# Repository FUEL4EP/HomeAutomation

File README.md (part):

# HomeAutomation   

## Home Automation Repository von FUEL4EP

### Homebrew [Asksinpp](https://asksinpp.de/) Sensoren und benötigtes [CCU3/openCCU Addon](https://github.com/FUEL4EP/HomeAutomation/releases/latest):

#### Sensoren:

|  | Name | Beschreibung | 🔋Batterie-/<br/>⚡️Netzbetrieb |
|--------|--------|--------|:--------:|
| | [HB-UNI-SENSOR1-CO2-SCD30](https://github.com/FUEL4EP/HomeAutomation/tree/master/AsksinPP_developments/sketches/HB-UNI-Sensor1-CO2_SCD30) | genauer NDIR CO2 Sensor<br/>_basierend auf Sensirion SCD30<br/>Akku- oder Netzbetrieb<br/>und WebUI Offseteinstellung_ | 🔋 ⚡ |
| | [HB-UNI-SENSOR1-AQ-BME680](https://github.com/FUEL4EP/HomeAutomation/tree/master/AsksinPP_developments/sketches/HB-UNI-Sensor1-AQ-BME680) | selbstkalibrierender Air Quality Sensor<br/>_basierend auf Bosch BME680<br/>und multipler linearer Regression<br/>und WebUI Offseteinstellung_ (aLF Version)| 🔋 |
| | [HB-UNI-SENSOR1-AQ-BME680_KF](https://github.com/FUEL4EP/HomeAutomation/tree/master/AsksinPP_developments/sketches/HB-UNI-Sensor1-AQ-BME680_KF) | selbst kalibrierender Air Quality Sensor<br/>basierend auf Bosch BME680<br/>und Kalman Filter<br/>und WebUI Offseteinstellung (aLF Version)| 🔋 |
| | [HB-UNI-SENSOR1-AQ-BME680_KF_DEBUG](https://github.com/FUEL4EP/HomeAutomation/tree/master/AsksinPP_developments/sketches/HB-UNI-Sensor1-AQ-BME680_KF_DEBUG) | selbst kalibrierender Air Quality Sensor<br/>basierend auf Bosch BME680<br/>und Kalman Filter<br/>und WebUI Offseteinstellung (aLF Version)<br/>nur für Debugzwecke!| 🔋 |
| | [HB-UNI-SENSOR1-TH-SHT75](https://github.com/FUEL4EP/HomeAutomation/tree/master/AsksinPP_developments/sketches/HB-UNI-Sensor1-TH-SHT75)  | hoch genauer TH Sensor<br/>_basierend auf Sensirion SHT75<br/>NEU: und 24h Tagesmittelwerttemperatur<br/>und WebUI Offseteinstellung_ | 🔋 |
| | [HB-UNI-SENSOR1-THPD-BME280](https://github.com/FUEL4EP/HomeAutomation/tree/master/AsksinPP_developments/sketches/HB-UNI-Sensor1-THPD-BME280) | THPD Sensor<br/>_basierend auf Bosch BME280<br/>mit Taupunkttemperatur<br/>und absoluter Luftfeuchte<br/>und WebUI Offseteinstellung_ | 🔋 |
| | [HB-UNI-SENSOR1-THPD-SHT85](https://github.com/FUEL4EP/HomeAutomation/tree/master/AsksinPP_developments/sketches/HB-UNI-Sensor1-THPD-SHT85)  | hoch genauer THPD Sensor<br/>_basierend auf Sensirion SHT85 und Bosch BME280<br/>mit Taupunkttemperatur<br/>und absoluter Luftfeuchte<br/>NEU: und 24h- und 7 Tagesmittelwerttemperaturen<br/>und WebUI Offseteinstellung_ | 🔋 |
| | [HB-UNI-SENSOR1-RAD-AL53](https://github.com/FUEL4EP/HomeAutomation/tree/master/AsksinPP_developments/sketches/HB-UNI-Sensor1-RAD-AL53) | Radioaktivitätssensor für Alpha-, Beta- und Gammastrahlung<br/>_basierend auf Teviso AL53 Sensor<br/>mit gleitender Mittelwertbildung über 7 Tage_ | 🔋 |
| | [HB-UNI-SENSOR1-AQ-BME680_KF_rLF](https://github.com/FUEL4EP/HomeAutomation/tree/master/AsksinPP_developments/sketches/HB-UNI-Sensor1-AQ-BME680_KF_rLF) <br/>- NEU -| selbstkalibrierender Air Quality Sensor<br/>basierend auf Bosch BME680<br/>und Kalman Filter<br/>und WebUI Offseteinstellung (rLF Version) | 🔋 |
| | [HB-UNI-SENSOR1-AQ-BME680_KF_rLF_DEBUG](https://github.com/FUEL4EP/HomeAutomation/tree/master/AsksinPP_developments/sketches/HB-UNI-Sensor1-AQ-BME680_KF_rLF_DEBUG) <br/>- NEU -| selbst kalibrierender Air Quality Sensor<br/>basierend auf Bosch BME680<br/>und Kalman Filter<br/>und WebUI Offseteinstellung (rLF Version)<br/>nur für Debugzwecke!| 🔋 |
| | [HB-UNI-SenAct-4-4-SC_DS](https://github.com/FUEL4EP/HomeAutomation/tree/master/AsksinPP_developments/sketches/HB-UNI-SenAct-4-4-SC_DS)<br/> - NEU -| 3x Schaltaktor für Betrieb an einem **Netzfreischalter** - Akkubetrieb im Standby, automatische Ladeschaltung - bei Aktivierung eines Aktors wird die Netzspannung zugeschaltet und am Ende wieder abgeschaltet - geringer Standby-Verbrauch von ca. 1 mA @ 5V| 🔋 ⚡ |
| | [HB-UNI-SENSOR1-THD-SHT45](https://github.com/FUEL4EP/HomeAutomation/tree/master/AsksinPP_developments/sketches/HB-UNI-Sensor1-THD-SHT45)<br/> - NEU -| hoch genauer THD Sensor<br/>basierend auf Sensirion SHT45 <br/>mit Taupunkttemperatur,<br/>absoluter Luftfeuchte<br/>und gleitendem Mittelwert der Temperatur über 24 Stunden und 7 Tage<br/>| 🔋 |
| | [HB-UNI-Sensor1-THPD-SHT45_BME280](https://github.com/FUEL4EP/HomeAutomation/tree/master/AsksinPP_developments/sketches/HB-UNI-Sensor1-THPD-SHT45_BME280)<br/> - NEU -| hoch genauer THPD Sensor<br/>basierend auf Sensirion SHT45 und Bosch BME280 <br/>mit Taupunkttemperatur,<br/>absoluter Luftfeuchte<br/>und gleitendem Mittelwert der Temperatur über 24 Stunden und 7 Tage<br/>| 🔋 |
| | [Range_test_beacon](https://github.com/FUEL4EP/HomeAutomation/tree/master/AsksinPP_developments/sketches/Range_test_beacon)<br/> - NEU -| 868,3Mhz Funkbake um die Reichweite eines HF-Übertragungskanals zu ermitteln (nur für Testzwecke)<br/>| 🔋 |
| | [FreqTest_range_test_with_distant_beacon](https://github.com/FUEL4EP/HomeAutomation/tree/master/AsksinPP_developments/sketches/FreqTest_range_test_with_distant_beacon)<br/> - NEU -| spezielle Version von FreqTest um die Reichweite eines HF-Übertragungskanals zu ermitteln (nur für Testzwecke)<br/>| 🔋 |
| | [HB-UNI-Sensor1-THP_MA-AHT20_BMP280](https://github.com/FUEL4EP/HomeAutomation/tree/master/AsksinPP_developments/sketches/HB-UNI-Sensor1-THP_MA-AHT20_BMP280)<br/> - NEU -|  genauer THP Außensensor zur Beobachtung des Klimawandels<br/>basierend auf Aosong AHT20 und Bosch BME280 <br/>mit gleitenden Temperaturmittelwerten für 1 Jahr, 1 Monat, 1 Woche und 1 Tag<br>mit nichtflüchtigem FRAM-Speicher| 🔋 |

<br/>
<br/>
<br/>

#### CCU3/openCCU Addon:

[hb-ep-devices-addon](https://github.com/FUEL4EP/HomeAutomation/releases/latest)

- bitte die .tgz Datei als Zusatzsoftware auf der CCU3/openCCU installieren

<br/>

#### Arduino Bibliotheken:

| Name | Beschreibung | Datenblatt |
|--------|--------|:--------:|
| [ABLIC_S35770](https://github.com/FUEL4EP/HomeAutomation/tree/master/AsksinPP_developments/libraries/ABLIC_S35770) | Arduino Bibliothek für ABLIC S-35770<br/>24-Bit Binärzähler mit I2C Schnittstelle | [datasheet](https://www.ablic.com/en/doc/datasheet/counter_ic/S35770_I_E.pdf)|
| [avr_stl](https://github.com/FUEL4EP/HomeAutomation/tree/master/AsksinPP_developments/libraries/avr_stl) | Arduino C++ Standard Library (ArduinoSTL)<br/>abgeleitet von [Giampaolo Mancini](https://github.com/manchoz/avr_stl.git) | [README.md](https://github.com/FUEL4EP/HomeAutomation/tree/master/AsksinPP_developments/libraries/avr_st/README.md)|
| [FRAM Bibliothek](https://github.com/FUEL4EP/HomeAutomation/tree/master/AsksinPP_developments/sketches/HB-UNI-Sensor1-THP_MA-AHT20_BMP280/Sensors/Fujitsu_MB85RS2MTPF_FRAM_circular_buffer.h) | Arduino C++ Bibliothek für Fujitsu 2x 2MBit MB85RS2MTPF SPI FRAM | Source Code |

<br/>

#### PCBs:

| Name | Beschreibung | 3D Ansicht |
|--------|--------|:--------:|
| [HB-UNI-SEN-BATT_FUEL4EP](https://github.com/FUEL4EP/HomeAutomation/tree/master/AsksinPP_developments/PCBs/HB-UNI-SEN-BATT_FUEL4EP) | AsksinPP Platine basierend auf [Tindie Pro Mini XL - v2 - ATmega 1284p](https://www.tindie.com/products/prominimicros/pro-mini-xl-v2-atmega-1284p/) oder Arduino Pro Mini| [3D Ansicht](https://github.com/FUEL4EP/HomeAutomation/tree/master/AsksinPP_developments/PCBs/HB-UNI-SEN-BATT_FUEL4EP/PNGs/HB-UNI-SEN-BATT_FUEL4EP_PCB_top_3D.png)|
| [HB-UNI-SEN-BATT_E07-868MS10_FUEL4EP](https://github.com/FUEL4EP/HomeAutomation/tree/master/AsksinPP_developments/PCBs/HB-UNI-SEN-BATT_E07-868MS10_FUEL4EP) | AsksinPP Platine basierend auf<br/> [Tindie Pro Mini XL - v2 - ATmega 1284p](https://www.tindie.com/products/prominimicros/pro-mini-xl-v2-atmega-1284p/) oder Arduino Pro Mini<br/> und [eByte E07-868MS10 Sendemodul](https://www.rcscomponents.kiev.ua/datasheets/e07-868ms10_usermanual_en_v1_20.pdf)| [3D Ansicht](https://github.com/FUEL4EP/HomeAutomation/tree/master/AsksinPP_developments/PCBs/HB-UNI-SEN-BATT_E07-868MS10_FUEL4EP/PNGs/HB-UNI-SEN-BATT_E07-868MS10_FUEL4EP_PCB_3D_top.png)|
| [HB-UNI-SEN-BATT_ATMega1284P_E07-900MM10S_FUEL4EP](https://github.com/FUEL4EP/HomeAutomation/tree/master/AsksinPP_developments/PCBs/HB-UNI-SEN-BATT_ATMega1284P_E07-900MM10S_FUEL4EP) | AsksinPP Platine mit SMD Bestückung:<br/> ATMega1284P <br/>[eByte E07-900MM10S Sendemodul](https://www.cdebyte.com/products/E07-900MM10S)<br/>optionalem Aufwärtwandler TPS61221<br/>[optionalem e-Paper Waveshare 1,54 Zoll](https://www.waveshare.com/wiki/1.54inch_e-Paper_Module)| [3D Ansicht 1](https://github.com/FUEL4EP/HomeAutomation/tree/master/AsksinPP_developments/PCBs/HB-UNI-SEN-BATT_ATMega1284P_E07-900MM10S_FUEL4EP/PNGs/HB-UNI-SEN-BATT_ATMega1284P_E07-900MM10S_FUEL4EP_PCB_top_3D.png)<br/>[3D Ansicht 2](https://github.com/FUEL4EP/HomeAutomation/tree/master/AsksinPP_developments/PCBs/HB-UNI-SEN-BATT_ATMega1284P_E07-900MM10S_FUEL4EP/PNGs/HB-UNI-SEN-BATT_ATMega1284P_E07-900MM10S_FUEL4EP_PCB_top_3D_with_epaper_option.png)|
| [HB-UNI-SEN-BATT_ATMega1284P_E07-868MS10_FUEL4EP](https://github.com/FUEL4EP/HomeAutomation/tree/master/AsksinPP_developments/PCBs/HB-UNI-SEN-BATT_ATMega1284P_E07-868MS10_FUEL4EP) | AsksinPP Platine mit SMD Bestückung:<br/> ATMega1284P <br/>[eByte E07-868MS10 Sendemodul](https://www.rcscomponents.kiev.ua/datasheets/e07-868ms10_usermanual_en_v1_20.pdf)<br/>optionalem Aufwärtwandler TPS61221<br/>[optionalem e-Paper Waveshare 1,54 Zoll](https://www.waveshare.com/wiki/1.54inch_e-Paper_Module)| [3D Ansicht 1](https://github.com/FUEL4EP/HomeAutomation/tree/master/AsksinPP_developments/PCBs/HB-UNI-SEN-BATT_ATMega1284P_E07-868MS10_FUEL4EP/PNGs/HB-UNI-SEN-BATT_ATMega1284P_E07-868MS10_FUEL4EP_PCB_top_3D.png)<br/>[3D Ansicht 2](https://github.com/FUEL4EP/HomeAutomation/tree/master/AsksinPP_developments/PCBs/HB-UNI-SEN-BATT_ATMega1284P_E07-868MS10_FUEL4EP/PNGs/HB-UNI-SEN-BATT_ATMega1284P_E07-868MS10_FUEL4EP_PCB_top_3D_with_epaper_option.png)|
| [HB-UNI-SEN-BATT_ATMega1284P_E07-868MS10_FRAM_FUEL4EP](https://github.com/FUEL4EP/HomeAutomation/tree/master/AsksinPP_developments/PCBs/HB-UNI-SEN-BATT_ATMega1284P_E07-868MS10_FRAM_FUEL4EP) | AsksinPP Platine mit SMD Bestückung:<br/> ATMega1284P <br/>[eByte E07-868MS10 Sendemodul](https://www.rcscomponents.kiev.ua/datasheets/e07-868ms10_usermanual_en_v1_20.pdf)<br/>optionalem Aufwärtwandler TPS61221<br/>[optionalem e-Paper Waveshare 1,54 Zoll](https://www.waveshare.com/wiki/1.54inch_e-Paper_Module)<br/>optionalen 2x 2Mbit FRAM MB85RS2MTPF| [3D Ansicht 1](https://github.com/FUEL4EP/HomeAutomation/tree/master/AsksinPP_developments/PCBs/HB-UNI-SEN-BATT_ATMega1284P_E07-868MS10_FRAM_FUEL4EP/PNGs/HB-UNI-SEN-BATT_ATMega1284P_E07-868MS10_FRAM_FUEL4EP_PCB_top_3D.png)<br/>[3D Ansicht 2](https://github.com/FUEL4EP/HomeAutomation/tree/master/AsksinPP_developments/PCBs/HB-UNI-SEN-BATT_ATMega1284P_E07-868MS10_FRAM_FUEL4EP/PNGs/HB-UNI-SEN-BATT_ATMega1284P_E07-868MS10_FRAM_FUEL4EP_PCB_with_epaper_option.png)|
| [HB-UNI-SenAct-4-4-SC_DS_FUEL4EP](https://github.com/FUEL4EP/HomeAutomation/tree/master/AsksinPP_developments/PCBs/HB-UNI-SenAct-4-4-SC_DS_FUEL4EP) | AsksinPP Platine für Durchsteckmontage für 3xSchaltaktor für Betrieb an Netzfreischalter| [3D Ansicht](https://github.com/FUEL4EP/HomeAutomation/tree/master/AsksinPP_developments/PCBs/HB-UNI-SenAct-4-4-SC_DS_FUEL4EP/PNGs/HB-UNI-SenAct-4-4-SC_DS_FUEL4EP_PCB_top_3D.png)|
| [HB-UNI-SEN-BATT_E07-900M10S_FUEL4EP](https://github.com/FUEL4EP/HomeAutomation/tree/master/AsksinPP_developments/PCBs/HB-UNI-SEN-BATT_E07-900M10S_FUEL4EP) - NEU -| AsksinPP Platine basierend auf<br/> [Tindie Pro Mini XL - v2 - ATmega 1284p](https://www.tindie.com/products/prominimicros/pro-mini-xl-v2-atmega-1284p/) oder Arduino Pro Mini<br/> und [eByte E07-900M10S Sendemodul](https://www.manualslib.com/manual/2937348/Ebyte-E07-900m10s.html)| [3D Ansicht](https://github.com/FUEL4EP/HomeAutomation/tree/master/AsksinPP_developments/PCBs/HB-UNI-SEN-BATT_E07-900M10S_FUEL4EP/PNGs/HB-UNI-SEN-BATT_E07-900M10S_FUEL4EP_PCB_3D_top.png)|
| [HB-UNI-SEN-BATT_E07-900MM10S_FUEL4EP](https://github.com/FUEL4EP/HomeAutomation/tree/master/AsksinPP_developments/PCBs/HB-UNI-SEN-BATT_E07-900MM10S_FUEL4EP) - NEU -| AsksinPP Platine basierend auf<br/> [Tindie Pro Mini XL - v2 - ATmega 1284p](https://www.tindie.com/products/prominimicros/pro-mini-xl-v2-atmega-1284p/) oder Arduino Pro Mini<br/> und [eByte E07-900MM10S Sendemodul](https://www.cdebyte.com/pdf-down.aspx?id=1932)| [3D Ansicht](https://github.com/FUEL4EP/HomeAutomation/tree/master/AsksinPP_developments/PCBs/HB-UNI-SEN-BATT_E07-900MM10S_FUEL4EP/PNGs/HB-UNI-SEN-BATT_E07-900MM10S_FUEL4EP_PCB_3D_top.png)|
| [CC1101_868MHz_RF_Modul_FUEL4EP](https://github.com/FUEL4EP/HomeAutomation/tree/master/AsksinPP_developments/PCBs/CC1101_868MHz_RF_Modul_FUEL4EP) - NEU -| AsksinPP RF 868.3 MHz Funkmodule als Ersatz für eByte E07-868M10S| [3D Ansicht](https://github.com/FUEL4EP/HomeAutomation/tree/master/AsksinPP_developments/PCBs/CC1101_868MHz_RF_Modul_FUEL4EP/PNGs/CC1101_868MHz_RF_Modul_FUEL4EP_PCB_3D_top.png)|
| [CC1101_868MHz_UFL_RF_Modul_FUEL4EP](https://github.com/FUEL4EP/HomeAutomation/tree/master/AsksinPP_developments/PCBs/CC1101_868MHz_UFL_RF_Modul_FUEL4EP) - NEU -| AsksinPP RF 868.3 MHz Funkmodule als Ersatz für eByte E07-868M10S mit U.FL Antennenbuchse| [3D Ansicht](https://github.com/FUEL4EP/HomeAutomation/tree/master/AsksinPP_developments/PCBs/CC1101_868MHz_UFL_RF_Modul_FUEL4EP/PNGs/CC1101_868MHz_UFL_RF_Modul_FUEL4EP_PCB_3D_top.png)|
| [4Bit_I2C_Port_Expander_Module_FUEL4EP](https://github.com/FUEL4EP/HomeAutomation/tree/master/AsksinPP_developments/PCBs/4Bit_I2C_Port_Expander_Module_FUEL4EP) - NEU -| I2C Portexpander| [3D Ansicht](https://github.com/FUEL4EP/HomeAutomation/tree/master/AsksinPP_developments/PCBs/4Bit_I2C_Port_Expander_Module_FUEL4EP/PNGs/4Bit_I2C_Port_Expander_Module_FUEL4EP_PCB_3D_top.png)|
| [I2C_Module_BME280_FUEL4EP](https://github.com/FUEL4EP/HomeAutomation/tree/master/AsksinPP_developments/PCBs/I2C_Module_BME280_FUEL4EP) - NEU -| I2C BME280 THPD Sensor Modul| [3D Ansicht](https://github.com/FUEL4EP/HomeAutomation/tree/master/AsksinPP_developments/PCBs/I2C_Module_BME280_FUEL4EP/PNGs/I2C_Module_BME280_FUEL4EP_PCB_3D_top.png)|
| [I2C_Module_BME680_FUEL4EP](https://github.com/FUEL4EP/HomeAutomation/tree/master/AsksinPP_developments/PCBs/I2C_Module_BME680_FUEL4EP) - NEU -| I2C BME680 VOC Sensor Modul| [3D Ansicht](https://github.com/FUEL4EP/HomeAutomation/tree/master/AsksinPP_developments/PCBs/I2C_Module_BME680_FUEL4EP/PNGs/I2C_Module_BME680_FUEL4EP_PCB_3D_top.png)|
| [I2C_Module_SHT85_BME280_FUEL4EP](https://github.com/FUEL4EP/HomeAutomation/tree/master/AsksinPP_developments/PCBs/I2C_Module_SHT85_BME280_FUEL4EP) - NEU -| I2C SHT85 und BME280 THPD Sensor Modul| [3D Ansicht](https://github.com/FUEL4EP/HomeAutomation/tree/master/AsksinPP_developments/PCBs/I2C_Module_SHT85_BME280_FUEL4EP/PNGs/I2C_Module_SHT85_BME280_FUEL4EP_PCB_3D_top.png)|
| [I2C_Module_SHT45_BME280_FUEL4EP](https://github.com/FUEL4EP/HomeAutomation/tree/master/AsksinPP_developments/PCBs/I2C_Module_SHT45_BME280_FUEL4EP) - NEU -| I2C SHT45 und BME280 THPD Sensor Modul| [3D Ansicht](https://github.com/FUEL4EP/HomeAutomation/tree/master/AsksinPP_developments/PCBs/I2C_Module_SHT45_BME280_FUEL4EP/PNGs/I2C_Module_SHT45_BME280_FUEL4EP_PCB_3D_top.png)|
| [I2C_Module_SHT45_BME280_small_FUEL4EP](https://github.com/FUEL4EP/HomeAutomation/tree/master/AsksinPP_developments/PCBs/I2C_Module_SHT45_BME280_small_FUEL4EP) - NEU -| kleines I2C SHT45 und BME280 THPD Sensor Modul| [3D Ansicht](https://github.com/FUEL4EP/HomeAutomation/tree/master/AsksinPP_developments/PCBs/I2C_Module_SHT45_BME280_small_FUEL4EP/PNGs/I2C_Module_SHT45_BME280_small_FUEL4EP_PCB_3D_top.png)|
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
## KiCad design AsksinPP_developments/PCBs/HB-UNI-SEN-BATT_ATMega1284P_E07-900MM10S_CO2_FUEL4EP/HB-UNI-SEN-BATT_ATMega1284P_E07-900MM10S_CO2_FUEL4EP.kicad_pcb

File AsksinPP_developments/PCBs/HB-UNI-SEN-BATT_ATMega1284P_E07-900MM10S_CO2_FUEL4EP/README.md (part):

# HB-UNI-SEN-BATT_ATMega1284P_E07-900MM10S_CO2_FUEL4EP    

# DO NOT USE: THE PCB HAS FATAL ERRORS AND MUST BE REWORKED: KiCAD symbol and footprint of the FDN304P were wrong. Furthermore, for the I2C pass gates the FDN304P's capacitances are by far too big. The control circuit shown in GSS' data sheet CozIR-Blink-DataSheet-Rev-4.25_3.pdf on page 8 is WRONG and does not work! A rework is ongoing. 
  
# BITTE NICHT BENUTZEN: Die Platine hat fatale Fehler und muss neu erstellt werden: KiCAD Symbol und Footprint des FDN304P MOSFET Transistors sind falsch. Außerdem sind die Kapazitäten eines FDN304P Transistors als I2C Passgate viel zu hoch. Die Kontrollschaltung, die in dem GSS Datenblatt CozIR-Blink-DataSheet-Rev-4.25_3.pdf auf Seite 8  gezeigt wird ist falsch und funktioniert so nicht! Eine Überarbeitung ist im Gange.

**Platine für DIY AsksinPP NDIR-CO2-Sensor COZIR-BLINK-5000 mit extrem niedrigem Stromverbrauch :**
- speziell angepasst für [COZIR-LP3-5000 CozIR®-LP3 Low Power CO2 Sensor](https://www.co2meter.com/de-de/collections/1-percent-co2-sensor/products/cozir-lp3-co2-sensor?variant=32074932781174)
	- der CO2 Sensor ist käuflich erwerbbar z.B. bei Reichelt [COZIR-BLINK-NON-PIN-5000](https://www.reichelt.de/de/de/shop/produkt/ultra-low_power_co2_sensor_mit_power-cycling-308788?PROVID=2788&gad_source=1&gad_campaignid=1622074784)
	- ein Datenblatt des CO2 Sensors ist [hier](https://cdn.shopify.com/s/files/1/0019/5952/files/CozIR-LP3_Data_Sheet_Rev_4.6.pdf?v=1695834654)
	- Messbereich bis 5000 ppm CO2
- eingebauter SMD TQFP-44 [ATMega1284P](https://ww1.microchip.com/downloads/en/DeviceDoc/doc8059.pdf) mit 128kByte Programmspeicher, 16kByte SRAM, 4kByte EEPROM
-  als Funkmodul wird das [eByte E07-900MM10S Sendemodul](https://ebyteiot.com/products/ebyte-e07-900MM10Sti-cc1101-wireless-rf-module-868mhz-915mhz-ipex-stamp?_pos=2&_sid=bbf1d47dc&_ss=r) verwendet.
- U.FL Antennenbuchse als Bestückungsoption für eine externe Antenne
- kleines 10mmx10mm [eByte E07-900MM10S Sendemodul](https://ebyteiot.com/products/ebyte-e07-900MM10Sti-cc1101-wireless-rf-module-868mhz-915mhz-ipex-stamp?_pos=2&_sid=bbf1d47dc&_ss=r)
- Steckerleiste für [Waveshare ePaper Modul (1.54inch (B)](https://www.waveshare.com/product/1.54inch-e-paper-module.htm)
- Bestückungsoption für [Waveshare ePaper Modul (1.54inch (B)](https://www.waveshare.com/product/1.54inch-e-paper-module.htm)
- Bestückungsoption für [TPS61221 Aufwärtswandler](https://www.ti.com/lit/ds/symlink/tps61221.pdf?ts=1634546965861&ref_url=https%253A%252F%252Fwww.ti.com%252Fproduct%252FTPS61221) bei NiMH Akkumulatorbetrieb
- die Bestückungsoptionen ePaper wurden noch nicht validiert!
- 3 LEDS für die Anzeige der CO2-Konzentration mit kurz aufblinkenden LEDs (rot, gelb, grün)
- Bestückungsoption für Piezosignalgeber [POPESQ® Signalgeber Piezo Buzzer 13x13x2.5mm](https://www.amazon.de/dp/B0C57D9RQ8) zur akustischen Warnung bei zu hoher CO2-Konzentration
- eingebauter [BOSCH BME280 I2C Sensor](https://www.bosch-sensortec.com/products/environmental-sensors/humidity-sensors-bme280/) zur Luftdruckkompensation des CO2-Sensors
- alle SMD Bausteine sind mit dem JLCPCB SMT Bestückungsservice kostengünstig und qualitativ hochwertig bestückbar

## Status

- die Platine wurde bei JLCPCB bestellt und ist nun in der Fertigung ist aber noch nicht validiert. Nutzung auf eigenes Risiko!

## Credits

- diese Platine ist von Alexander Reinerts Platine [HB-UNI-SEN-BATT](https://github.com/alexreinert/PCB/tree/master/HB-UNI-SEN-BATT) abgeleitet.
- vielen Dank an Alexander Reinert für die Vorarbeit
- der Abstand der Batteriehalter wurde vergrößert, damit der COZIR-LP3-5000 CozIR®-LP3 Low Power CO2 Sensor dazwischen passt.

## Eigenschaften

- abgeleitet aus [HB-UNI-SEN-BATT](https://github.com/alexreinert/PCB/tree/master/HB-UNI-SEN-BATT)
- kompletter Datensatz für KiCAD 8 auf Github verfügbar:
    + 'git clone https://github.com/FUEL4EP/HomeAutomation.git' oder als [ZIP-Datei](https://github.com/FUEL4EP/HomeAutomation/archive/refs/heads/master.zip)
    + die Platinendaten sind dann unter 'HomeAutomation/AsksinPP_developments/PCBs/HB-UNI-SEN-BATT_ATMega1284P_E07-900MM10S_CO2_FUEL4EP' direkt mit KiCAD aufrufbar
- neue Eigenschaften:
    + SMD Bestückung, wo möglich
    + SMD TQFP-44 [ATMega1284P](https://ww1.microchip.com/downloads/en/DeviceDoc/doc8059.pdf) mit 128kByte Programmspeicher, 16kByte SRAM, 4kByte EEPROM
    + Bestückungsoption für [Waveshare ePaper Modul (1.54inch (B)](https://www.waveshare.com/product/1.54inch-e-paper-module.htm)
    + Bestückungsoption für [TPS61221 Aufwärtswandler](https://www.ti.com/lit/ds/symlink/tps61221.pdf?ts=1634546965861&ref_url=https%253A%252F%252Fwww.ti.com%252Fproduct%252FTPS61221) bei NiMH Akkumulatorbetrieb
    + alle SMD Bausteine sind mit dem JLCPCB SMT Bestückungsservice kostengünstig und qualitativ hochwertig bestückbar, das ist also auch für Grobmotoriker wie mich geeignet :-)
    + Stiftleiste J10 mit Versorgungsspannungen zum Gehäuseoberteil oder Akkulademodul
    + als Funkmodul wird das [eByte E07-900MM10S Sendemodul](https://ebyteiot.com/products/ebyte-e07-900MM10Sti-cc1101-wireless-rf-module-868mhz-915mhz-ipex-stamp?_pos=2&_sid=bbf1d47dc&_ss=r) verwendet. Dieses ist qualitativ viel besser als die üblichen grünen noname 868 MHz Funkmodule.
    + das schafft Platz für eine 8-polige Stiftleiste J11 zum optionalen Anschluss eines [Waveshare ePaper Moduls (1.54inch (B)](https://www.waveshare.com/product/1.54inch-e-paper-module.htm). Der ATMega1284P hat auch genügend RAM für die Programmierung eines 200 Pixel x 200 Pixel e-Papermoduls.
    + JLCPCB BOM and CPL Dateien für SMT Service werden [bereitgestellt](./jlcpcb/production_files)

### Benötigte Bauteile:

- bedingt durch die SMT Service von JLCPCB sind nur noch wenige Durchsteckbauteile von Hand zu verlöten:
* e-Paper [Waveshare ePaper Moduls (1.54inch (B)](https://www.waveshare.com/product/1.54inch-e-paper-module.htm) (optional, Anschluss an J11)
* CO2 Sensor [COZIR-LP3-5000 CozIR®-LP3 Low Power CO2 Sensor](https://www.co2meter.com/de-de/collections/1-percent-co2-sensor/products/cozir-lp3-co2-sensor?variant=32074932781174)
* Piezosignalgeber [Amazon POPESQ® Signalgeber Piezo Buzzer 13x13x2.5mm](https://www.amazon.de/dp/B0C57D9RQ8) oder [Alibaba 13*13 MM SMD-Summer-Wandler Extern angetriebener Piezo 5 V 5 mA 4,1 kHz 75 dB Oberflächen montierte Lötpads FUET-1325 Piezo-Summer](https://www.alibaba.com/product-detail/13-13-MM-SMD-Buzzer-Transducer_62560653672.html)
* 2x Keystone 2460 Batteriehalter 1xAA, z.B. [SOS Electronic](https://www.soselectronic.com/de-de/products/keystone-electronics/keys2460-2460-135729)
* Stiftleiste RM 2mm 1x8 Pin (für ePaper)
* Stiftleisten RM 2,54mm (nach Bedarf)
* IRLU024N (optional für Verpolungsschutz)
* Versorgung durch NiMH Akkumulatoren und Aufwärtswandler ist vorbereitet (JP2)
* Bestückungsoption Aufwärtswandler siehe [Schaltplan](Schematics/HB-UNI-SEN-BATT_ATMega1284P_E07-900MM10S_CO2_FUEL4EP.pdf), unter KiCAD sind alle Referenzen eingetragen

### Aufbauhinweise

- es wird dringend angeraten, vor dem Einbau der I2C Sensoren durchzuführen
    + einen Frequenztest. Hier der Frequenztest für einen ATmega 1284p : [FreqTest_1284P.ino](../Supplements/FreqTest_1284P/FreqTest_1284P.ino)
    + einen Leckagetest. Hier der Leckagetest für einen ATmega 1284p : [SleepTest_1284P.ino](../Supplements/SleepTest_1284P/SleepTest_1284P.ino)
        + der Leckagestrom im Sleepmode sollte < 10 uA betragen

### Passende AsksinPP Projekte von FUEL4EP
   + [tbd](https://github.com/FUEL4EP/HomeAutomation/tree/master/AsksinPP_developments/sketches/tbd)
   + muss noch entwickelt werden

### Anschluss eines FTDI Debuggers

- zum Anschluss eines FTDI Debuggers an die 6-polige Stiftleiste J12 bitte ein [6 Pin Dupontkabel 2.54mm Buchse-Buchse 20 cm](https://www.roboter-bausatz.de/p/6-pin-dupontkabel-2.54mm-buchse-buchse-20-cm) verwenden

### Passendes Gehäuse
* tbd, muss noch entwickelt werden

### Hinweise
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
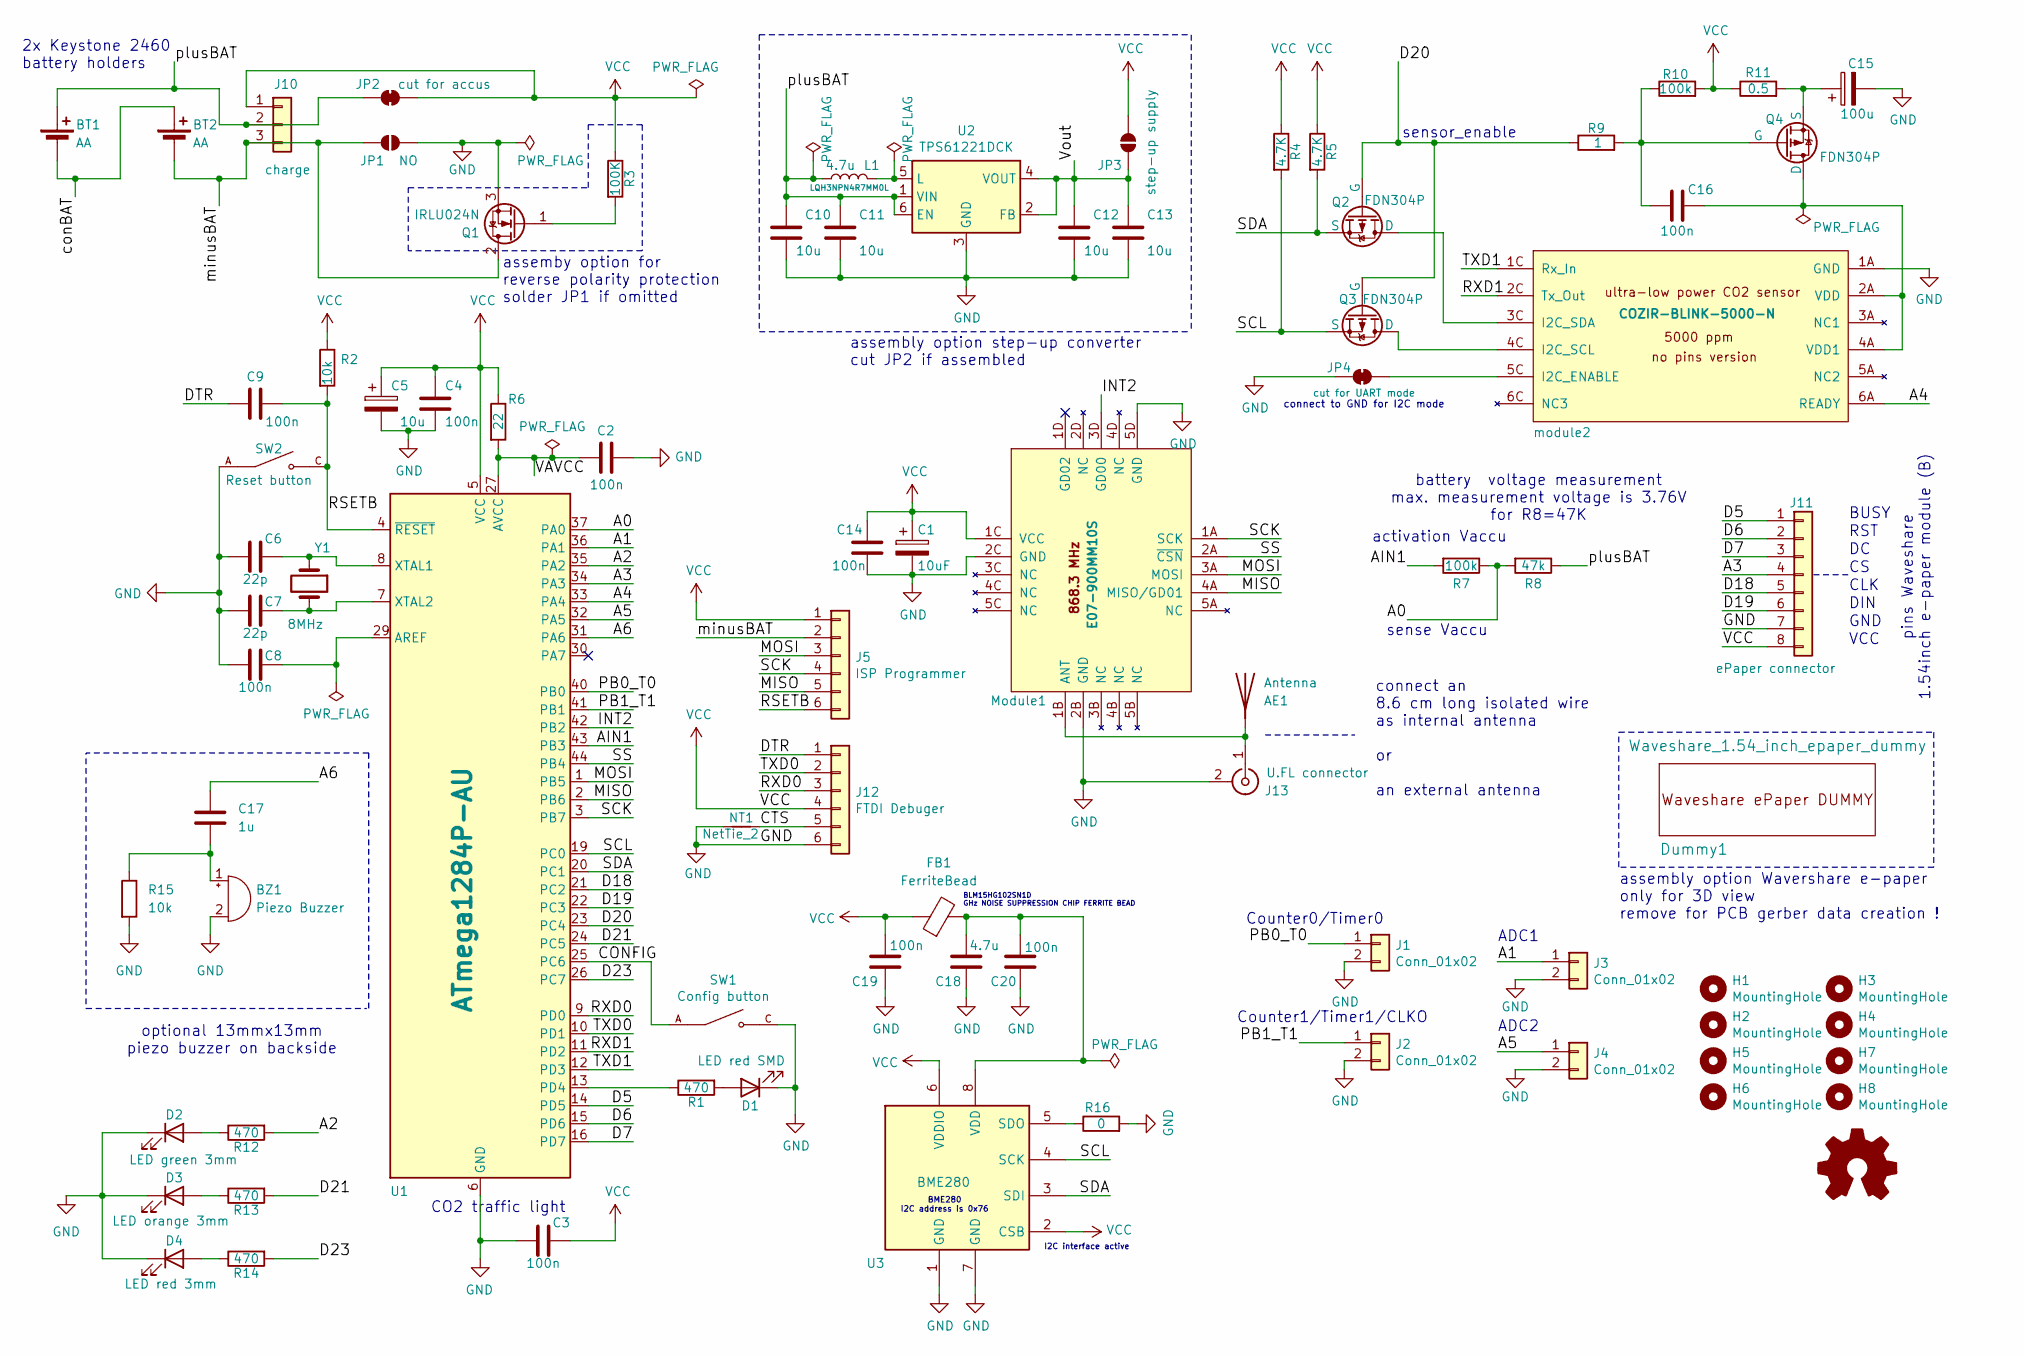
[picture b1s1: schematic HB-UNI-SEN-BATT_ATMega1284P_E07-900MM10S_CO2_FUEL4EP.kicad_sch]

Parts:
AE1: Antenna; SolderWire-0.1sqmm_1x01_D0.4mm_OD1mm
BT1, BT2: AA; BatteryHolder_Keystone_2460_1xAA
BZ1: Piezo Buzzer; Buzzer_SMD_POPESQ_POPESQ_13mm_13mm_2.5mm
C1: 10uF; C_0402_1005Metric; LCSC C15525
C2, C3, C4, C8, C9: 100n; C_0805_2012Metric; LCSC C28233
C5: 10u; C_1206_3216Metric_Pad1.33x1.80mm_HandSolder; LCSC C7171
C6, C7: 22p; C_0805_2012Metric; LCSC C1804
C10, C11, C12, C13: 10u; C_0805_2012Metric; LCSC C15850
C14: 100n; C_0402_1005Metric; LCSC C1525
C15: 100u; CP_EIA-6032-15_Kemet-U_Pad2.25x2.35mm_HandSolder; LCSC C16133
C16, C19, C20: 100n; C_0603_1608Metric; LCSC C14663
C17: 1u; C_0805_2012Metric_Pad1.18x1.45mm_HandSolder; LCSC C28323
C18: 4.7u; C_0603_1608Metric; LCSC C19666
D1: LED red SMD; LED_0805_2012Metric_Pad1.15x1.40mm_HandSolder; LCSC C84256
D2: LED green 3mm; LED_D3.0mm_angle_green
D3: LED orange 3mm; LED_D3.0mm_angle_orange
D4: LED red 3mm; LED_D3.0mm_angle_red
Dummy1: Waveshare_1.54_inch_epaper_dummy; Waveshare_ePaper_module
FB1: FerriteBead; L_0402_1005Metric; LCSC C76889
H1, H2, H3, H4: MountingHole; MountingHole_2.2mm_M2_Pad_Via
H5, H6, H7, H8: MountingHole; ePaper_MountingHole_M5
J1, J2, J3, J4: Conn_01x02; PinHeader_1x02_P2.54mm_Vertical
J5: ISP Programmer; PinHeader_1x06_P2.54mm_Vertical
J10: charge; PinHeader_1x03_P2.54mm_Vertical
J11: ePaper connector; PinSocket_1x08_P2.00mm_Vertical
J12: FTDI Debuger; PinHeader_1x06_P2.54mm_Vertical
J13: U.FL connector; U.FL_Molex_MCRF_73412-0110_Vertical
JP1: NO; SolderJumper-2_P1.3mm_Open_Pad1.0x1.5mm
JP2: cut for accus; SolderJumper-2_P1.3mm_Bridged_Pad1.0x1.5mm
JP3: step-up supply; SolderJumper-2_P1.3mm_Open_Pad1.0x1.5mm
JP4: cut for UART mode; SolderJumper-2_P1.3mm_Bridged_Pad1.0x1.5mm
L1: 4.7u; FUEL4EP_Inductor_SMD_1; LCSC C86077
LOGO1: Logo_Open_Hardware_Small; CC-BY-ND-SA
Module1: E07-900MM10S; eByte_E07-900MM10S; LCSC C5844212
NT1: NetTie_2; NetTie-2_SMD_Pad0.5mm
Q1: IRLU024N; TO-251-3_Vertical; LCSC C558184
Q2, Q3, Q4: FDN304P; SOT-23; LCSC C241803
R1, R12, R13, R14: 470; R_0805_2012Metric_Pad1.20x1.40mm_HandSolder; LCSC C17710
R2, R15: 10k; R_0805_2012Metric_Pad1.20x1.40mm_HandSolder; LCSC C17414
R3: 100K; R_0603_1608Metric_Pad0.98x0.95mm_HandSolder; LCSC C25803
R4, R5: 4.7K; R_0805_2012Metric_Pad1.20x1.40mm_HandSolder; LCSC C17673
R6: 22; R_0805_2012Metric_Pad1.20x1.40mm_HandSolder; LCSC C23345
R7: 100k; R_0805_2012Metric_Pad1.20x1.40mm_HandSolder; LCSC C149504
R8: 47k; R_0805_2012Metric_Pad1.20x1.40mm_HandSolder; LCSC C17713
R9: 1; R_0603_1608Metric; LCSC C22936
R10: 100k; R_0603_1608Metric; LCSC C25803
R11: 0.5; R_0603_1608Metric; LCSC C45312
R16: 0; R_0402_1005Metric; LCSC C17168
SW1: Config button; SW_TS-1187A-B-A-B; PARTREV A0; LCSC C318884
SW2: Reset button; SW_TS-1187A-B-A-B; PARTREV A0; LCSC C318884
U1: ATmega1284P-AU; TQFP-44_10x10mm_P0.8mm; LCSC C33575
U2: TPS61221DCK; Texas_R-PDSO-G6; LCSC C37055
U3: BME280; Bosch_LGA-8_2.5x2.5mm_P0.65mm_ClockwisePinNumbering; LCSC C92489
Y1: 8MHz; Crystal_SMD_5032-2Pin_5.0x3.2mm_HandSoldering; LCSC C115962
module2: COZIR-BLINK-5000-N

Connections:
/A0: R7.1, R8.2, U1.37 (PA0)
/A1: J3.1, U1.36 (PA1)
/A2: R12.2, U1.35 (PA2)
/A3: J11.4, U1.34 (PA3)
/A4: U1.33 (PA4), module2.6A (READY)
/A5: J4.1, U1.32 (PA5)
/A6: C17.1, U1.31 (PA6)
/AIN1: R7.2, U1.43 (PB3)
/CONFIG: SW1.A, SW1.B (e), U1.25 (PC6)
/CTS: J12.5, NT1.2
/D5: J11.1, U1.14 (PD5)
/D6: J11.2, U1.15 (PD6)
/D7: J11.3, U1.16 (PD7)
/D18: J11.5, U1.21 (PC2)
/D19: J11.6, U1.22 (PC3)
/D20: Q2.2 (G), Q3.2 (G), R9.1, U1.23 (PC4)
/D21: R13.2, U1.24 (PC5)
/D23: R14.2, U1.26 (PC7)
/DTR: C9.2, J12.1
/INT2: Module1.3D (GD00), U1.42 (PB2)
/MISO: J5.5, Module1.4A (MISO/GD01), U1.2 (PB6)
/MOSI: J5.3, Module1.3A (MOSI), U1.1 (PB5)
/PB0_T0: J1.1, U1.40 (PB0)
/PB1_T1: J2.1, U1.41 (PB1)
/RSETB: C9.1, J5.6, R2.2, SW2.C, SW2.D, U1.4 (~RESET)
/RXD0: J12.3, U1.9 (PD0)
/RXD1: U1.11 (PD2), module2.2C (Tx_Out)
/SCK: J5.4, Module1.1A (SCK), U1.3 (PB7)
/SCL: Q3.3 (S), R4.2, U1.19 (PC0), U3.4 (SCK)
/SDA: Q2.3 (S), R5.2, U1.20 (PC1), U3.3 (SDI)
/SS: Module1.2A (~CSN), U1.44 (PB4)
/TXD0: J12.2, U1.10 (PD1)
/TXD1: U1.12 (PD3), module2.1C (Rx_In)
/VAVCC: C2.2, R6.2, U1.27 (AVCC)
/Vout: C12.1, C13.1, JP3.1 (A), U2.2 (FB), U2.4 (VOUT)
/conBAT: BT1.2 (-), BT2.1 (+)
/minusBAT: BT2.2 (-), J5.2, J10.3, JP1.1 (A), Q1.2 (D)
/plusBAT: BT1.1 (+), C10.1, C11.1, J10.2, JP2.1 (A), L1.1, R8.1, U2.1 (VIN), U2.6 (EN)
GND: BZ1.2 (-), C1.2, C2.1, C3.2, C4.2, C5.2, C6.2, C7.2, C8.2, C10.2, C11.2, C12.2, C13.2, C14.2, C15.2, C18.2, C19.2, C20.2, D1.1 (K), D2.1 (K), D3.1 (K), D4.1 (K), J1.2, J2.2, J3.2, J4.2, J11.7, J12.6, J13.2 (Ext), JP1.2 (B), JP4.1 (A), Module1.2B (GND), Module1.2C (GND), Module1.5D (GND), NT1.1, Q1.3 (S), R15.2, R16.2, SW1.C, SW1.D, SW2.A, SW2.B (e), U1.6 (GND), U1.18 (GND), U1.28 (GND), U1.39 (GND), U2.3 (GND), U3.1 (GND), U3.7 (GND), module2.1A (GND)
unnamed: AE1.1 (A), J13.1 (In), Module1.1B (ANT)
unnamed: BZ1.1 (+), C17.2, R15.1
unnamed: D1.2 (A), R1.2
unnamed: D2.2 (A), R12.1
unnamed: D3.2 (A), R13.1
unnamed: D4.2 (A), R14.1
unnamed: JP4.2 (B), module2.5C (I2C_ENABLE)
unnamed: Q1.1 (G), R3.2
unnamed: Q2.1 (D), module2.3C (I2C_SDA)
unnamed: Q3.1 (D), module2.4C (I2C_SCL)
unnamed: C16.2, Q4.1 (D), module2.2A (VDD), module2.4A (VDD1)
unnamed: C16.1, Q4.2 (G), R9.2, R10.1
unnamed: C15.1, Q4.3 (S), R11.2
unnamed: C8.1, U1.29 (AREF)
unnamed: R1.1, U1.13 (PD4)
unnamed: C6.1, U1.8 (XTAL1), Y1.1
unnamed: C7.1, U1.7 (XTAL2), Y1.2
unnamed: L1.2, U2.5 (L)
unnamed: R16.1, U3.5 (SDO)
unnamed: C18.1, C20.1, FB1.2, U3.8 (VDD)
VCC: C1.1, C3.1, C4.1, C5.1, C14.1, C19.1, FB1.1, J5.1, J10.1, J11.8, J12.4, JP2.2 (B), JP3.2 (B), Module1.1C (VCC), R2.1, R3.1, R4.1, R5.1, R6.1, R10.2, R11.1, U1.5 (VCC), U1.17 (VCC), U1.38 (VCC), U3.2 (CSB), U3.6 (VDDIO)

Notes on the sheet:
connect to GND for I2C mode
RST
CLK
ADC2
connect an 8.6 cm long isolated wire as internal antenna or an external antenna
VCC
BME280 I2C address is 0x76
activation Vaccu
Counter1/Timer1/CLKO
assemby option for reverse polarity protection solder JP1 if omitted
BLM15HG102SN1D GHz NOISE SUPPRESSION CHIP FERRITE BEAD
Counter0/Timer0
ADC1
assembly option step-up converter cut JP2 if assembled
battery voltage measurement max. measurement voltage is 3.76V for R8=47K
pins Waveshare 1.54inch e-paper module (B)
sensor_enable
sense Vaccu
optional 13mmx13mm piezo buzzer on backside
2x Keystone 2460 battery holders
CO2 traffic light
GND
DIN
BUSY
I2C interface active
assembly option Wavershare e-paper only for 3D view remove for PCB gerber data creation !

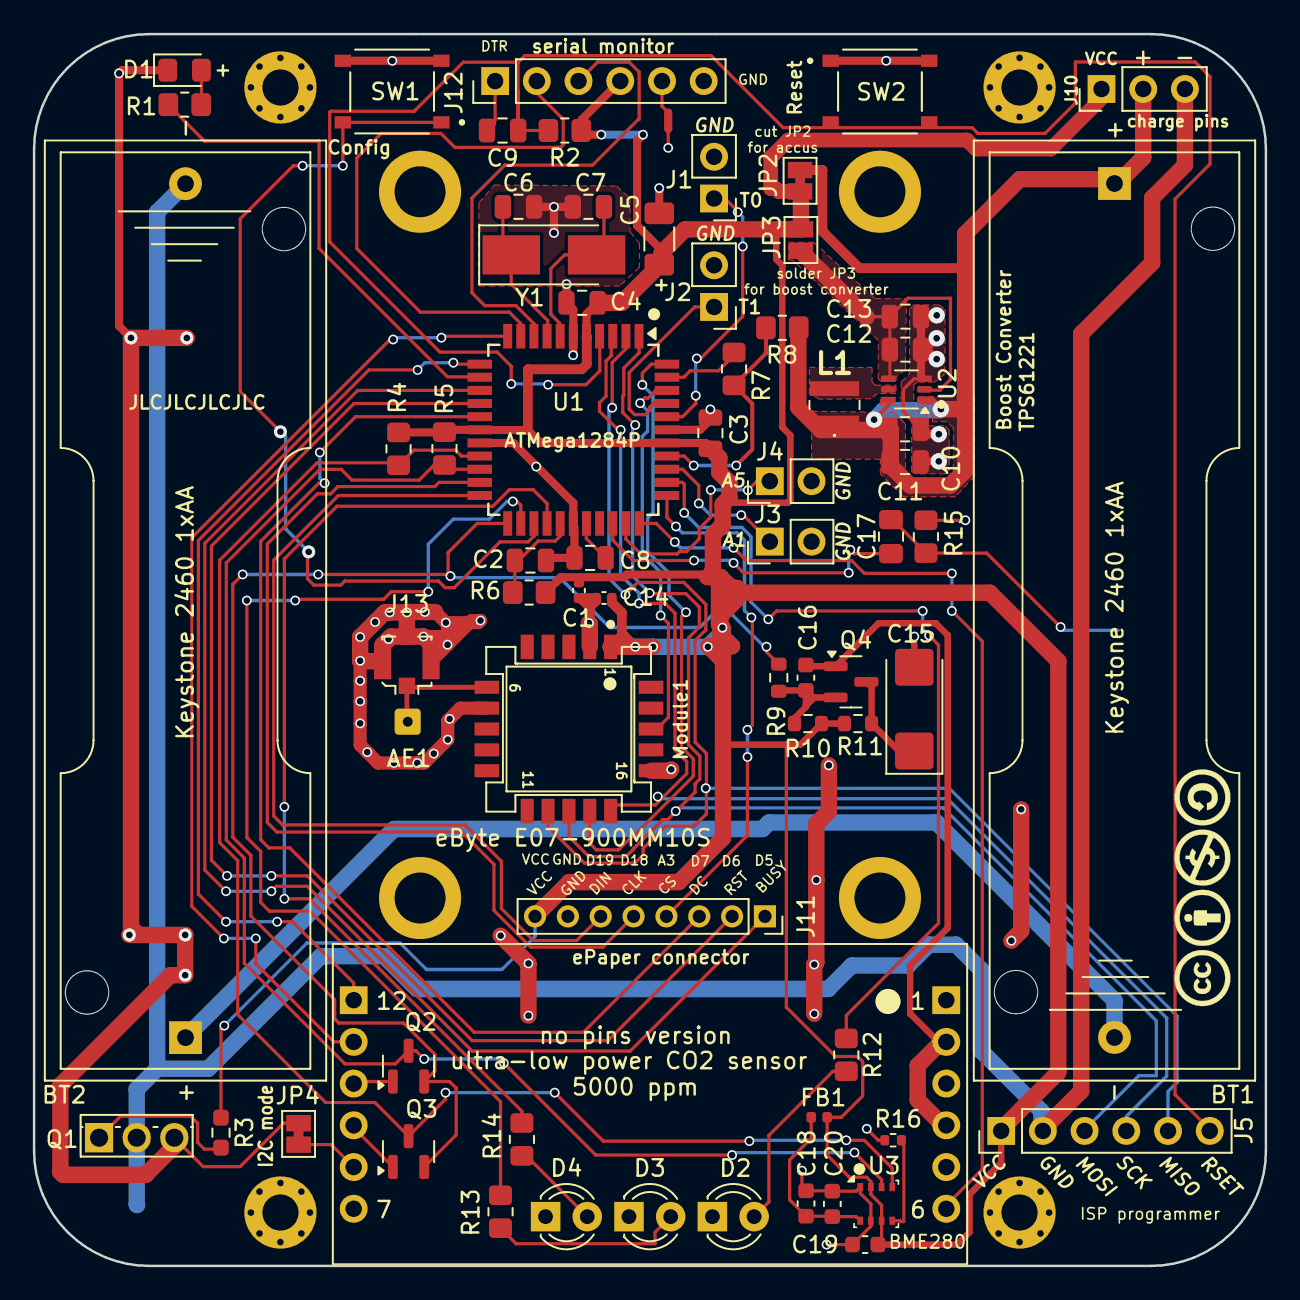
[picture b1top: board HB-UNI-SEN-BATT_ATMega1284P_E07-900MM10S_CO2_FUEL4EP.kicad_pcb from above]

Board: 2 copper layers, 75.0 x 75.0 mm, 81 parts (1 on the bottom side), 60 nets.

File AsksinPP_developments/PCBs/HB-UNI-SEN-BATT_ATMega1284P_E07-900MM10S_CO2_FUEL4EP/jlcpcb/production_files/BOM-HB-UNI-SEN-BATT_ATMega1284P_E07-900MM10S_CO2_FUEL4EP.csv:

Comment,Designator,Footprint,LCSC,Quantity
0,R16,R_0402_1005Metric,C17168,1
0.5,R11,R_0603_1608Metric,C45312,1
1,R9,R_0603_1608Metric,C22936,1
100K,R3,R_0603_1608Metric_Pad0.98x0.95mm_HandSolder,C25803,1
100k,R7,R_0805_2012Metric_Pad1.20x1.40mm_HandSolder,C149504,1
100k,R10,R_0603_1608Metric,C25803,1
100n,"C16,C19,C20",C_0603_1608Metric,C14663,3
100n,C14,C_0402_1005Metric,C1525,1
100n,"C2,C3,C4,C8,C9",C_0805_2012Metric,C28233,5
100u,C15,CP_EIA-6032-15_Kemet-U_Pad2.25x2.35mm_HandSolder,C16133,1
10k,"R15,R2",R_0805_2012Metric_Pad1.20x1.40mm_HandSolder,C17414,2
10u,"C10,C11,C12,C13",C_0805_2012Metric,C15850,4
10u,C5,C_1206_3216Metric_Pad1.33x1.80mm_HandSolder,C7171,1
10uF,C1,C_0402_1005Metric,C15525,1
1u,C17,C_0805_2012Metric_Pad1.18x1.45mm_HandSolder,C28323,1
22,R6,R_0805_2012Metric_Pad1.20x1.40mm_HandSolder,C23345,1
22p,"C6,C7",C_0805_2012Metric,C1804,2
4.7K,"R4,R5",R_0805_2012Metric_Pad1.20x1.40mm_HandSolder,C17673,2
4.7u,C18,C_0603_1608Metric,C19666,1
4.7u,L1,FUEL4EP_Inductor_SMD_1,C86077,1
470,"R1,R12,R13,R14",R_0805_2012Metric_Pad1.20x1.40mm_HandSolder,C17710,4
47k,R8,R_0805_2012Metric_Pad1.20x1.40mm_HandSolder,C17713,1
8MHz,Y1,Crystal_SMD_5032-2Pin_5.0x3.2mm_HandSoldering,C115962,1
ATmega1284P-AU,U1,TQFP-44_10x10mm_P0.8mm,C33575,1
BME280,U3,Bosch_LGA-8_2.5x2.5mm_P0.65mm_ClockwisePinNumbering,C92489,1
Config button,SW1,SW_TS-1187A-B-A-B,C318884,1
E07-900MM10S,Module1,eByte_E07-900MM10S,C5844212,1
FDN304P,"Q2,Q3,Q4",SOT-23,C241803,3
FerriteBead,FB1,L_0402_1005Metric,C76889,1
IRLU024N,Q1,TO-251-3_Vertical,C558184,1
LED red SMD,D1,LED_0805_2012Metric_Pad1.15x1.40mm_HandSolder,C84256,1
Reset button,SW2,SW_TS-1187A-B-A-B,C318884,1
TPS61221DCK,U2,Texas_R-PDSO-G6,C37055,1
U.FL connector,J13,U.FL_Molex_MCRF_73412-0110_Vertical,C598199,1
Conn_01x02,J3,PinHeader_1x02_P2.54mm_Vertical,,1
Conn_01x02,J4,PinHeader_1x02_P2.54mm_Vertical,,1
ISP Programmer,J5,PinHeader_1x06_P2.54mm_Vertical,,1
charge,J10,PinHeader_1x03_P2.54mm_Vertical,,1
NO,JP1,SolderJumper-2_P1.3mm_Open_Pad1.0x1.5mm,,1
cut for accus,JP2,SolderJumper-2_P1.3mm_Bridged_Pad1.0x1.5mm,,1
FTDI Debuger,J12,PinHeader_1x06_P2.54mm_Vertical,,1
ePaper connector,J11,PinSocket_1x08_P2.00mm_Vertical,,1
step-up supply,JP3,SolderJumper-2_P1.3mm_Open_Pad1.0x1.5mm,,1
Conn_01x02,J1,PinHeader_1x02_P2.54mm_Vertical,,1
Conn_01x02,J2,PinHeader_1x02_P2.54mm_Vertical,,1
Antenna,AE1,SolderWire-0.1sqmm_1x01_D0.4mm_OD1mm,,1
COZIR-BLINK-5000-N,module2,COZIR-BLINK-5000-N,,1
cut for UART mode,JP4,SolderJumper-2_P1.3mm_Bridged_Pad1.0x1.5mm,,1
LED green 3mm,D2,LED_D3.0mm_angle_green,,1
LED orange 3mm,D3,LED_D3.0mm_angle_orange,,1
LED red 3mm,D4,LED_D3.0mm_angle_red,,1
Piezo Buzzer,BZ1,Buzzer_SMD_POPESQ_POPESQ_13mm_13mm_2.5mm,,1

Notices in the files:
AsksinPP_developments/PCBs/Adapter_EByte_E07_900MM10S_to_noname_green_RF_module_FUEL4EP/README.md:
License: CC BY-NC-SA 4.0
AsksinPP_developments/PCBs/HB-UNI-SEN-BATT_ATMega1284P_E07-900MM10S_CO2_FUEL4EP/HB-UNI-SEN-BATT_ATMega1284P_E07-900MM10S_CO2_FUEL4EP.kicad_sch:
Creative Commons License, non-commercial
AsksinPP_developments/PCBs/HB-UNI-SEN-BATT_E07-868MS10_FUEL4EP/HB-UNI-SEN-BATT_E07-868MS10_FUEL4EP.kicad_sch:
fork of Alexander Reinert's HB-UNI-SEN-BATT/ Creative Commons License,non-commercial
